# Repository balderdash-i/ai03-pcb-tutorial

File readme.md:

# ai03 PCB Tutorial Files
Created using the tutorial/guide found here:
https://wiki.ai03.com/books/pcb-design/chapter/pcb-designer-guide

I wouldn't recommend picking these files up and ordering PCB's - while they are correct and working to the best of my knowledge, this is the first time I've made a PCB from scratch. Consider at minimum reviewing my work.

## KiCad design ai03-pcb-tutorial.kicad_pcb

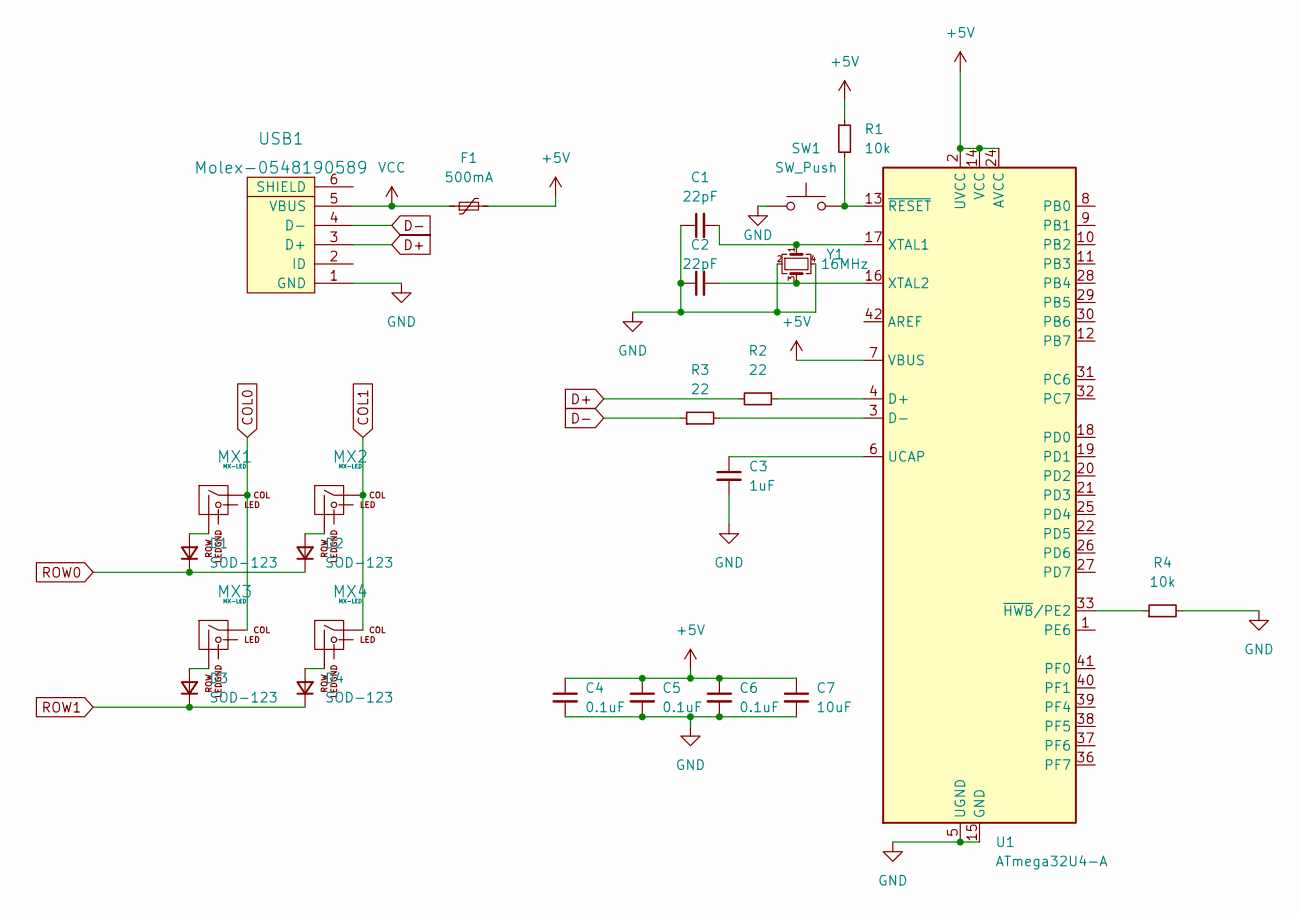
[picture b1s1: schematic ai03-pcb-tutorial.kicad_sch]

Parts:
C1, C2: 22pF; C_0805_2012Metric
C3: 1uF; C_0805_2012Metric
C4, C5, C6: 0.1uF; C_0805_2012Metric
C7: 10uF; C_0805_2012Metric
D1, D2, D3, D4: SOD-123; D_SOD-123
F1: 500mA; Fuse_1206_3216Metric
MX1, MX2, MX3, MX4: MX-LED; MX-1U
R1, R4: 10k; R_0805_2012Metric
R2, R3: 22; R_0805_2012Metric
SW1: SW_Push; SKQG-1155865
U1: ATmega32U4-A; TQFP-44_10x10mm_P0.8mm
USB1: Molex-0548190589
Y1: 16MHz; Crystal_SMD_3225-4Pin_3.2x2.5mm

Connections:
+5V: C4.1, C5.1, C6.1, C7.1, F1.2, R1.1, U1.2 (UVCC), U1.7 (VBUS), U1.14 (VCC), U1.24 (AVCC), U1.34 (VCC), U1.44 (AVCC)
COL0: MX1.1 (COL), MX3.1 (COL), U1.30 (PB6)
COL1: MX2.1 (COL), MX4.1 (COL), U1.29 (PB5)
D+: R2.2, USB1.3 (D+)
D-: R3.1, USB1.4 (D-)
GND: C1.1, C2.1, C3.2, C4.2, C5.2, C6.2, C7.2, R4.2, SW1.1, U1.5 (UGND), U1.15 (GND), U1.23 (GND), U1.35 (GND), U1.43 (GND), USB1.1 (GND), Y1.2, Y1.4
unnamed: C1.2, U1.17 (XTAL1), Y1.1
unnamed: C2.2, U1.16 (XTAL2), Y1.3
unnamed: C3.1, U1.6 (UCAP)
unnamed: D1.2 (A), MX1.2 (ROW)
unnamed: D2.2 (A), MX2.2 (ROW)
unnamed: D3.2 (A), MX3.2 (ROW)
unnamed: D4.2 (A), MX4.2 (ROW)
unnamed: R1.2, SW1.2, U1.13 (~RESET)
unnamed: R2.1, U1.4 (D+)
unnamed: R3.2, U1.3 (D-)
unnamed: R4.1, U1.33 (~HWB/PE2)
ROW0: D1.1 (K), D2.1 (K), U1.32 (PC7)
ROW1: D3.1 (K), D4.1 (K), U1.31 (PC6)
VCC: F1.1, USB1.5 (VBUS)

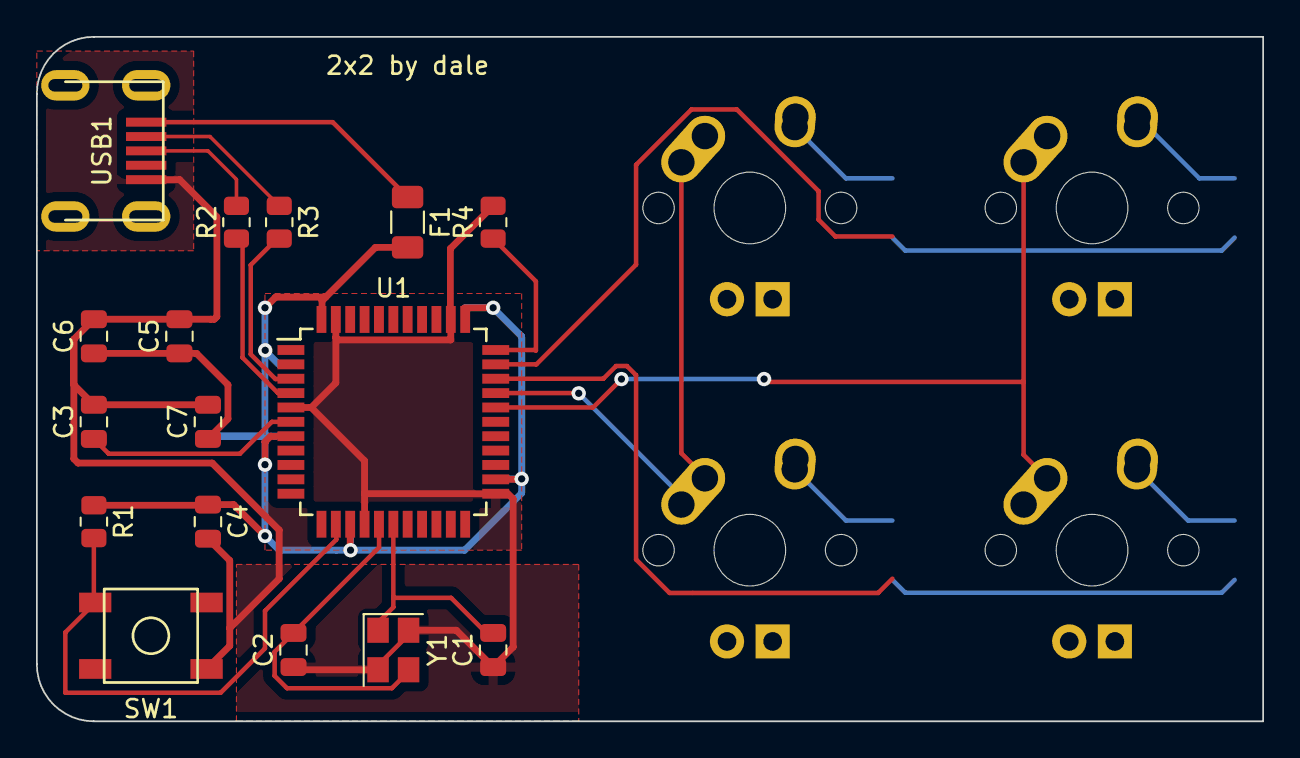
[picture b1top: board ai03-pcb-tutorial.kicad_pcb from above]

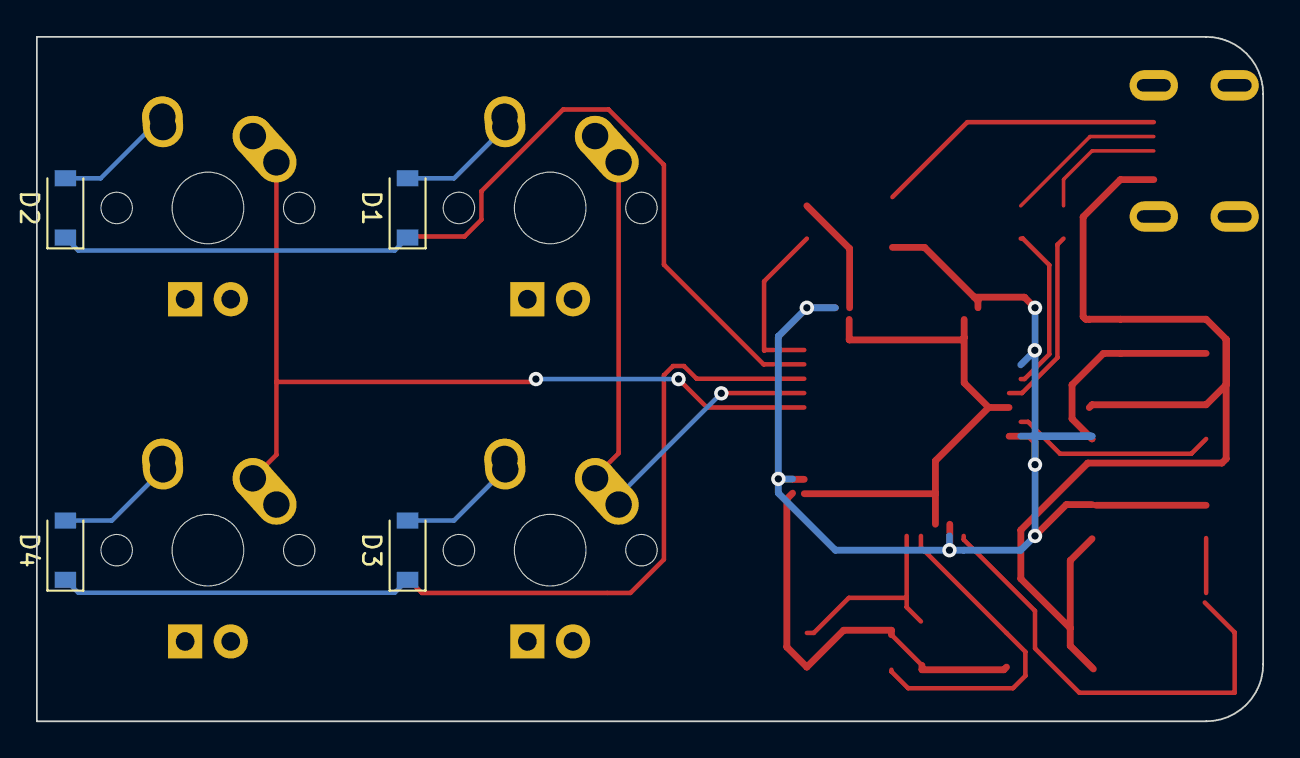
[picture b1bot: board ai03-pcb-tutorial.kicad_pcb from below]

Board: 2 copper layers, 68.3 x 38.1 mm, 24 parts (4 on the bottom side), 20 nets.

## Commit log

2022-12-18 Initial commit. Start with empty kicad files
2022-12-18 Add submodules
2022-12-18 Add symbol and footprint libraries for keyboards.
2022-12-18 Add completed MCU zone for Teensy
2022-12-18 Add usb and 2x2 MX key schematic
2022-12-18 Add footprint bindings for all schematic items
2022-12-18 All traces added, potentialy a working board
2022-12-18 Add gerbers
2022-12-18 Fix discontinuity in cut layer
2022-12-18 Add readme.
